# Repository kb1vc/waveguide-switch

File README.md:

# Description:

This is an OpenSCAD model for a positioner using a model airplane
servo to control a WR90 waveguide switch.

There are four major components in the SCAD file, each may be
printed separately.

The base holds the servo, a magnet to "capture" the positioning
slug, and two mounts for optical sensors that signal proper alignment
and positioning of the slug.

The slug connects to the shaft of the waveguide switch.  The slug
has two "vanes" that hold small magnets to latch the assembly into
the transmit or receive position.

The cap covers and protects the positioner and associated control
electronics.

For optimal performance, add a stripe of white or copper paint to
the "outside" edge of the slug vanes to provide a strong positive
reflection when the slug is in position.

---------
Arduino sketch
---------

The arduino sketch is written for the module described in the "module"
subdirectory. It is based on the Sparkfun Aruino Pro Mini. 

# License:
See the LICENSE.txt file for copyright and conditions for re-use.

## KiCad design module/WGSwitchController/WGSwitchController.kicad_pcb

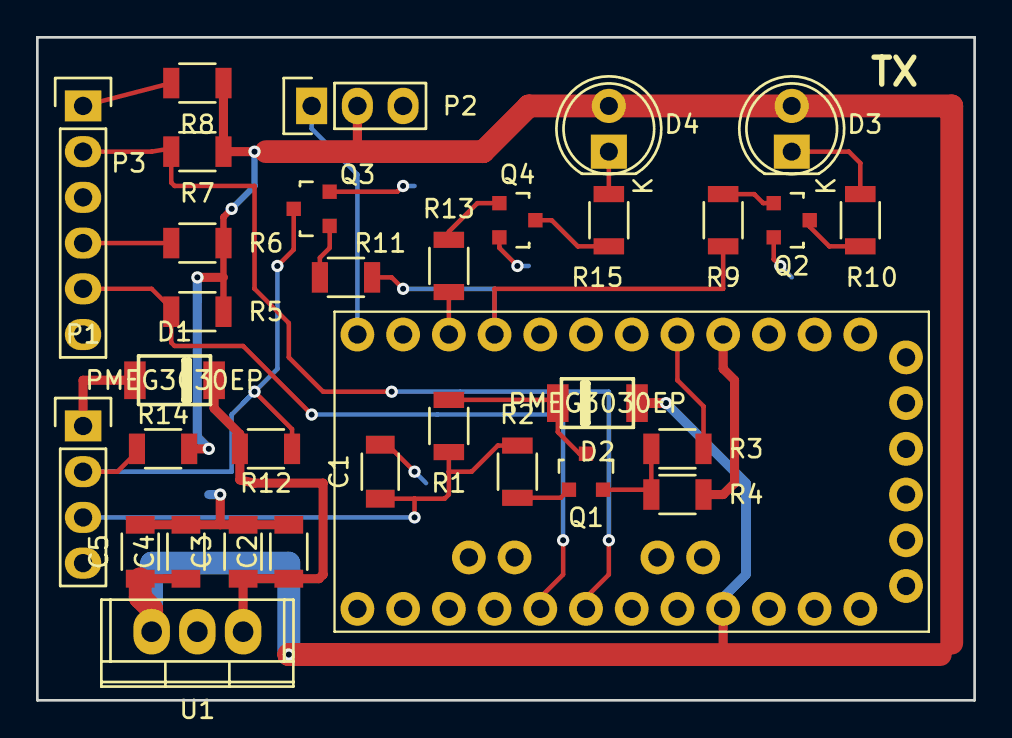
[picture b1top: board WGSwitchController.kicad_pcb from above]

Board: 2 copper layers, 52.1 x 36.8 mm, 33 parts (0 on the bottom side), 24 nets.

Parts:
C1: C; C_1206
C2, C4: 0.1; C_1206
C3, C5: 10; C_1206
D1, D2: PMEG3030EP; SOD-128
D3: GRN LED; LED-5MM
D4: RED LED; LED-5MM
M1: ARDUINO_PRO_MINI
P1: CONN_01X04; Pin_Header_Straight_1x04
P2: CONN_01X03; Pin_Header_Straight_1x03
P3: CONN_01X06; Pin_Header_Straight_1x06
Q1: MMBT3906; SOT-23
Q2, Q3, Q4: MMBT3904; SOT-23
R1, R2, R3, R4, R5, R7, R9, R11, R12, R13, R14: 10K; R_1206
R6, R8: 68; R_1206
R10, R15: 220; R_1206
U1: LM7805CT; TO-220

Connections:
+5V: C4.1, C5.1, D2.2, D3.2, D4.2, M1.21, P2.2, R5.1, R6.1, R7.1, R8.1, R14.1, U1.3
+12V: C2.1, C3.1, D1.1, R12.1, U1.1
GND: C1.2, C2.2, C3.2, C4.2, C5.2, M1.4, M1.23, P1.4, P2.3, P3.3, P3.6, Q2.2, Q3.2, Q4.2, R3.2, U1.2
unnamed: D1.2, P1.1
unnamed: D2.1, Q1.3, R1.2
unnamed: D3.1, R10.1
unnamed: D4.1, R15.1
unnamed: M1.12, P2.1
unnamed: P3.1, R8.2
unnamed: P3.4, R6.2
unnamed: Q1.1, R2.1
unnamed: Q1.2, R3.1, R4.2
unnamed: Q2.1, R9.1
unnamed: Q2.3, R10.2
unnamed: Q3.1, R11.1
unnamed: Q4.1, R13.1
unnamed: Q4.3, R15.2
PTT_IN_RAW_L: C1.1, P1.3, R1.1, R2.2
RX_ON: M1.10, R13.2
RX_SENSE: M1.18, P3.2, R7.2
TX_EN_IN_H: M1.5, R4.1
TX_EN_OUT_L: P1.2, Q3.3, R12.2, R14.2
TX_ON: M1.9, R9.2, R11.2
TX_SENSE: M1.17, P3.5, R5.2

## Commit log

2017-01-19 Almost there.
2017-01-21 New trial -- reduce slug height
2017-01-21 Final proto?
2017-01-28 Made cover... adjusted base.
2017-02-20 Added controller sketch, and new PC module.
2017-02-21 Added optical sensors. Trimmed slug to fit them.
2017-02-21 added text to readme
2017-02-22 Added hole and tabs for connector mount
2017-02-23 Added mount for connector.
2017-02-23 added article source
2017-02-23 added picture of trial and error.
2017-03-05 update sketch to work with full module.
2017-03-11 Added Sleep Mode version
2017-03-11 Bumped IR sensor thresholds to handle dark envelope.
2017-03-11 cleanup and optimize TRSwitchSleep to eliminate extra delay.
2017-03-15 more progress -- added images
2017-03-15 more progress
2017-03-18 Just about right.
2017-03-18 Got the spacing right, it seems
2017-03-18 First draft done.
2017-03-20 Ready for the proceedings?
2017-03-21 missing file -- added it.
2017-04-15 Saving the module... this will be rev B.
2017-04-15 Rev C of module -- fixed diode footprints.

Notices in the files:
module/WGSwitchController/WGSwitchController.kicad_pcb:
CC BY-SA 4.0
